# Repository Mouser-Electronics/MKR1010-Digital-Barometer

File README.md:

# MKR1010 Digital Galileo Thermometer and Glass Globe Barometer

A digital version of a Galileo thermometer and glass globe barometer using the Arduino MKR1010. Leveraging the BMP280 I2C Barometric Pressure/Temperature Sensor, an 8x8 NeoPixel matrix, and a blower fan to create a fun yet useful modern take on the antique weather monitoring technology. Demonstration of IoT capability using the MediumOne IoT cloud platform using MQTT protocols.

 https://www.mouser.com/applications/modern-take-galileos-thermometer-geothes-barometer/

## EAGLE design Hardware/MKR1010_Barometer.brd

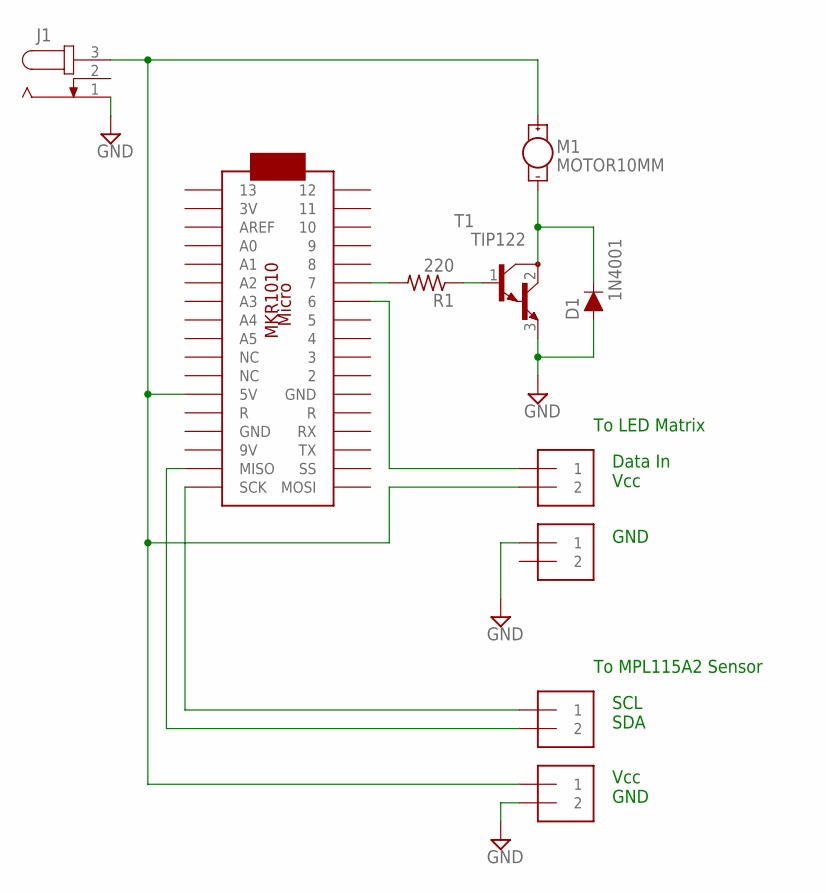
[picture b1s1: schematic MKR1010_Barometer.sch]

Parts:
D1: 1N4001; DIODE-1N4001
J1: JACK-PLUG0; SPC4077
J2, J3, J4, J5: 1X2-3.5MM
M1: MOTOR10MM; VIBE-MOTOR-10MM
MKR1010: ARDUINOMICRO
R1: 220; 0207/12
T1: TIP122; TO220

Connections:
GND: D1.A, J1.1, J3.1, J5.2, T1.3 (E)
unnamed: MKR1010.P$6 (7), R1.2
unnamed: R1.1, T1.1 (B)
unnamed: D1.C, M1.-, T1.2 (C)
unnamed: J1.3, J2.2, J5.1, M1.+, MKR1010.P$23 (5V)
unnamed: J2.1, MKR1010.P$7 (6)
unnamed: J4.1, MKR1010.P$18 (SCK)
unnamed: J4.2, MKR1010.P$19 (MISO)

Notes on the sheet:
MKR1010
To LED Matrix
To MPL115A2 Sensor
Data In Vcc
GND
SCL SDA
Vcc GND

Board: 2 copper layers, 10 parts (0 on the bottom side), 8 nets, no tracks yet.

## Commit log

2018-11-08 init commit
2018-11-08 baseline software functionality
    does not yet include connecting to cloud services
2018-11-08 communicate to MediumOne via MQTT
2018-11-08 changed previous temperature var (prevTemperatureC) into a static float
2018-11-09 schematic capture
2018-11-09 remove schematic backups
2018-11-10 added terminal to attach MPL115A2
2018-11-10 minor formatting updates
2018-11-11 cleanup code
2018-11-11 example of header file to store secret info
2018-11-11 changed int fansSpeed to static int fanSpeed
2018-11-15 Switch from REST to MQTT, BMP280 temp/press sensor
2018-11-15 update var names for SSID and SSID Key
2018-11-15 Updated schematic with BMP280
2018-11-16 Switch from WiFi101.h library to WiFININA.h for the MKR1010
    MKR1000 uses the WiFi101 library to communicate between the M0+ chip and WiFi. The MKR1010 uses the WiFiNINA.h library.
2018-11-16 adjusted LED brightness to make dimmer
2018-11-18 Created variable for High/Low Pressure and High/Low Fan Speed

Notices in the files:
parts and their libraries:
SparkFun-DiscreteSemi: Licensing: Creative Commons ShareAlike 4.0 International - https://creativecommons.org/licenses/by-sa/4.0
